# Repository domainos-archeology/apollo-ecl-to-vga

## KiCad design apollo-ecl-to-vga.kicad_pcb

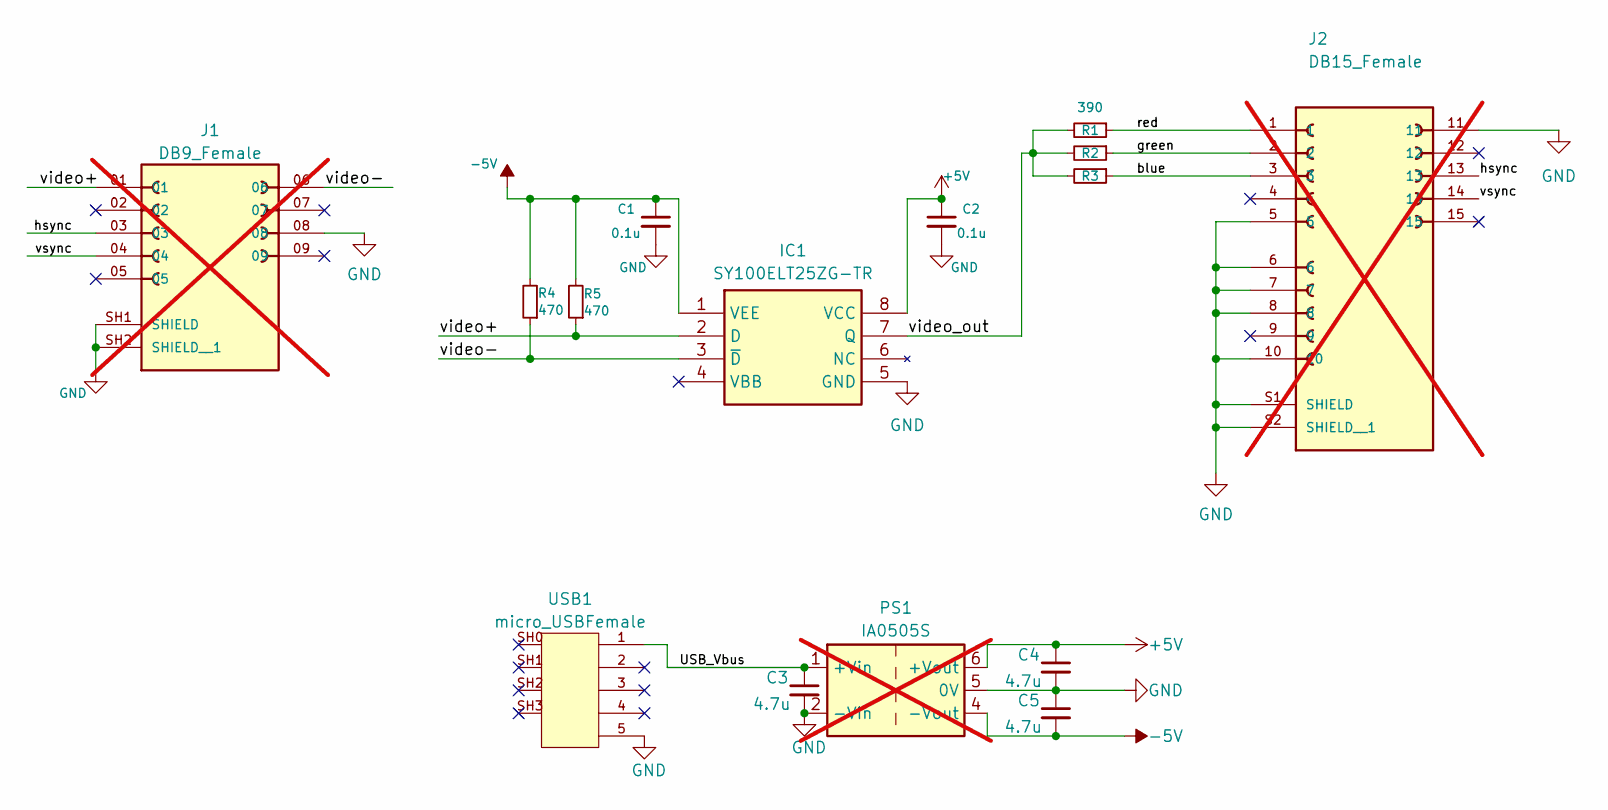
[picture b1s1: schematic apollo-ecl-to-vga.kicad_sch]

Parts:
C1: 0.1u; R_0603_1608Metric
C2: 0.1u; C_0603_1608Metric
C3, C4, C5: 4.7u; C_0603_1608Metric
IC1: SY100ELT25ZG-TR; SOIC127P602X173-8N; Mouser Part Number 998-SY100ELT25ZGTR
J1: DB9_Female; AMPHENOL_LD09S13A4GV00LF; PARTREV B; not fitted
J2: DB15_Female; AMPHENOL_ICD15S13E4GX00LF; PARTREV G; not fitted
PS1: IA0505S; Converter_DCDC_XP_POWER-IAxxxxS_THT; LCSC C131042; not fitted
R1, R2, R3: 390; R_0603_1608Metric
R4, R5: 470; R_0603_1608Metric
USB1: micro_USBFemale; MICRO-USB-SMD_5P-P0.65-H-F_C10418; LCSC C10418

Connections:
+5V: C2.1, C4.1, IC1.8 (VCC), PS1.6 (+Vout)
-5V: C1.1, C5.2, IC1.1 (VEE), PS1.4 (-Vout), R4.2, R5.2
/USB_Vbus: C3.1, PS1.1 (+Vin), USB1.1 (V+)
/blue: J2.3, R3.1
/green: J2.2, R2.1
/hsync: J1.03, J2.13
/red: J2.1, R1.1
/video+: IC1.2 (D), J1.01, R5.1
/video-: IC1.3 (~D), J1.06, R4.1
/video_out: IC1.7 (Q), R1.2, R2.2, R3.2
/vsync: J1.04, J2.14
GND: C1.2, C2.2, C3.2, C4.2, C5.1, IC1.5 (GND), J1.08, J1.SH1 (SHIELD), J1.SH2 (SHIELD__1), J2.5, J2.6, J2.7, J2.8, J2.10, J2.11, J2.S1 (SHIELD), J2.S2 (SHIELD__1), PS1.2 (-Vin), PS1.5 (0V), USB1.5 (V-)

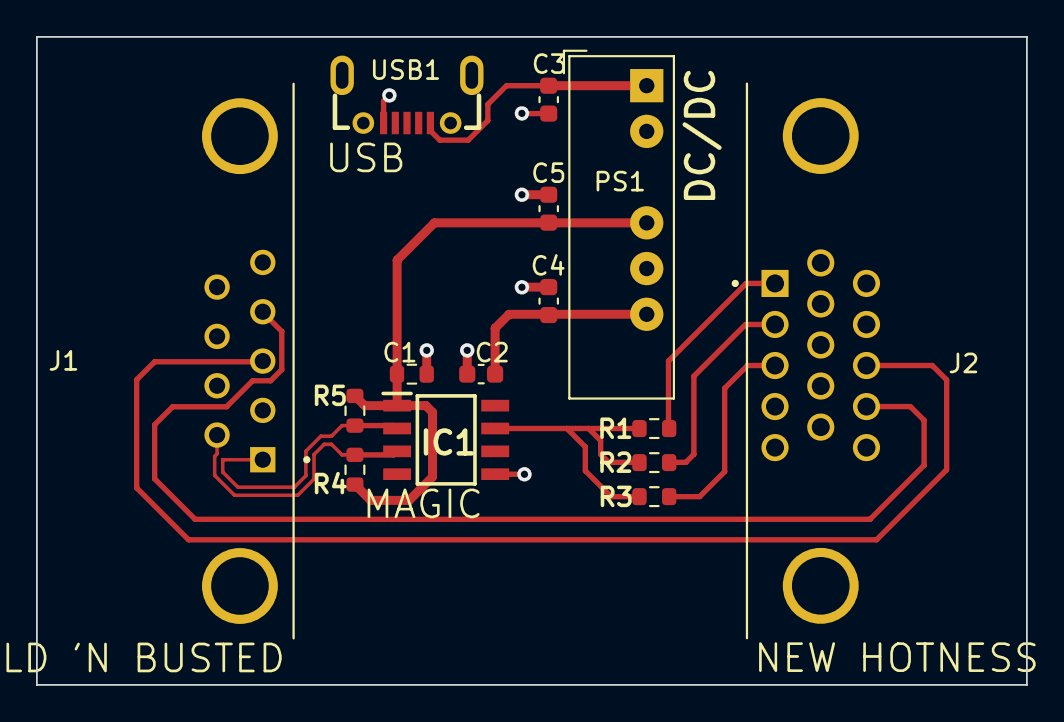
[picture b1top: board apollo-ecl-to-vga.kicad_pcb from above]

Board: 2 copper layers, 55.0 x 36.0 mm, 15 parts (0 on the bottom side), 12 nets.

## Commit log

2023-05-11 rev1
2023-05-17 label nets from usb connector
2023-05-17 add more resistors
2023-05-17 route sync_gnd on the back
2023-05-22 more futzing
2023-06-12 single GND. move things (vias, resistors, DC/DC) a touch to clean up routing, and cleanup some trace widths
2023-06-15 switch from 0805 to 0603 since they're being assembled anyway
